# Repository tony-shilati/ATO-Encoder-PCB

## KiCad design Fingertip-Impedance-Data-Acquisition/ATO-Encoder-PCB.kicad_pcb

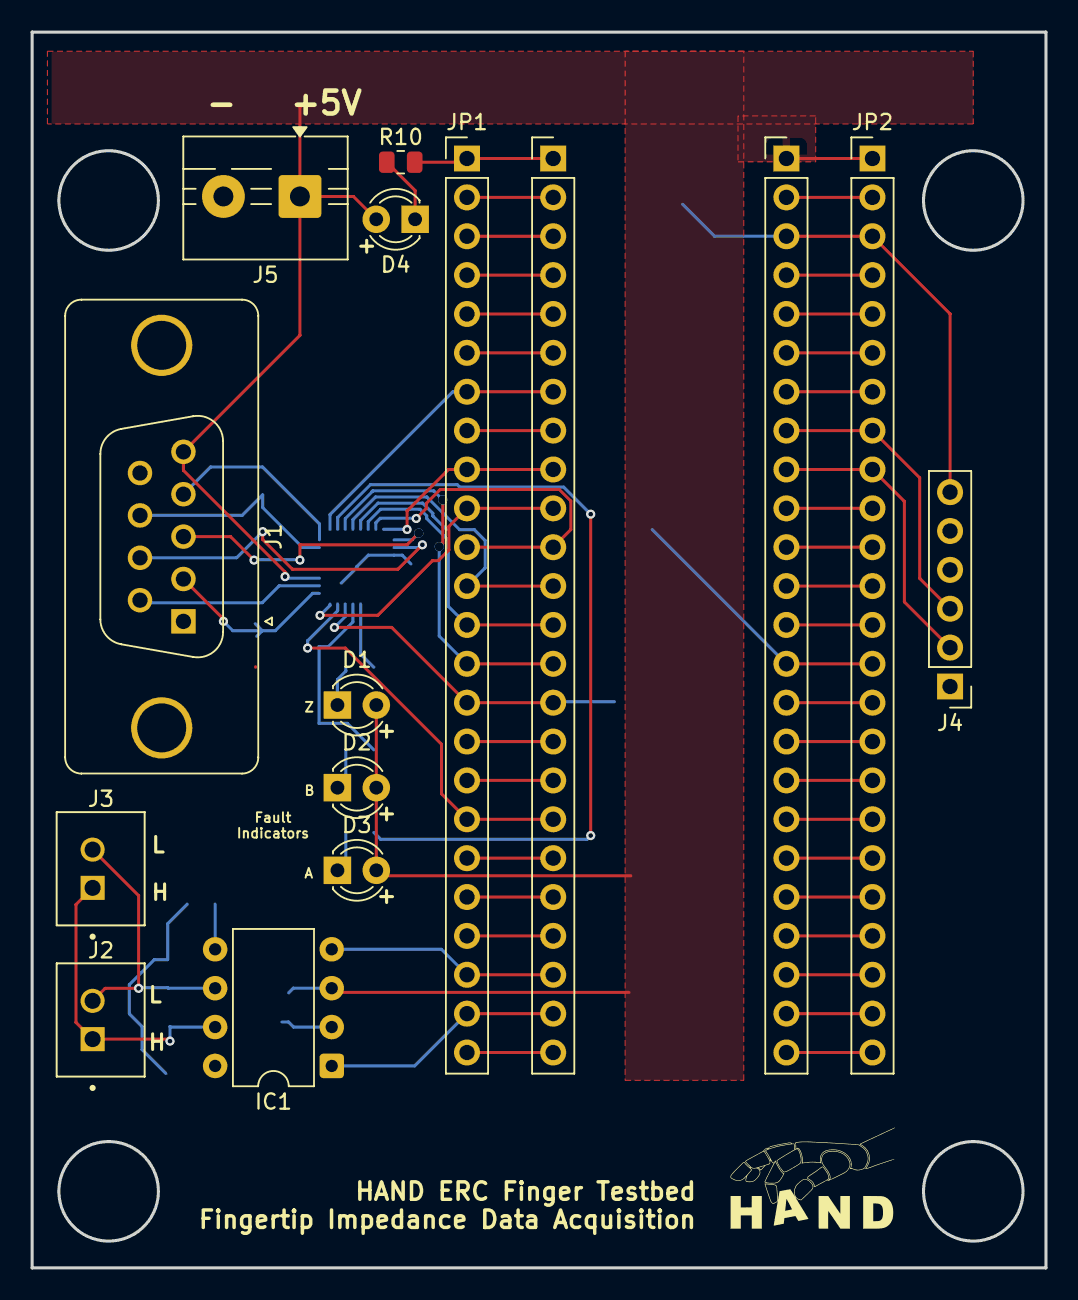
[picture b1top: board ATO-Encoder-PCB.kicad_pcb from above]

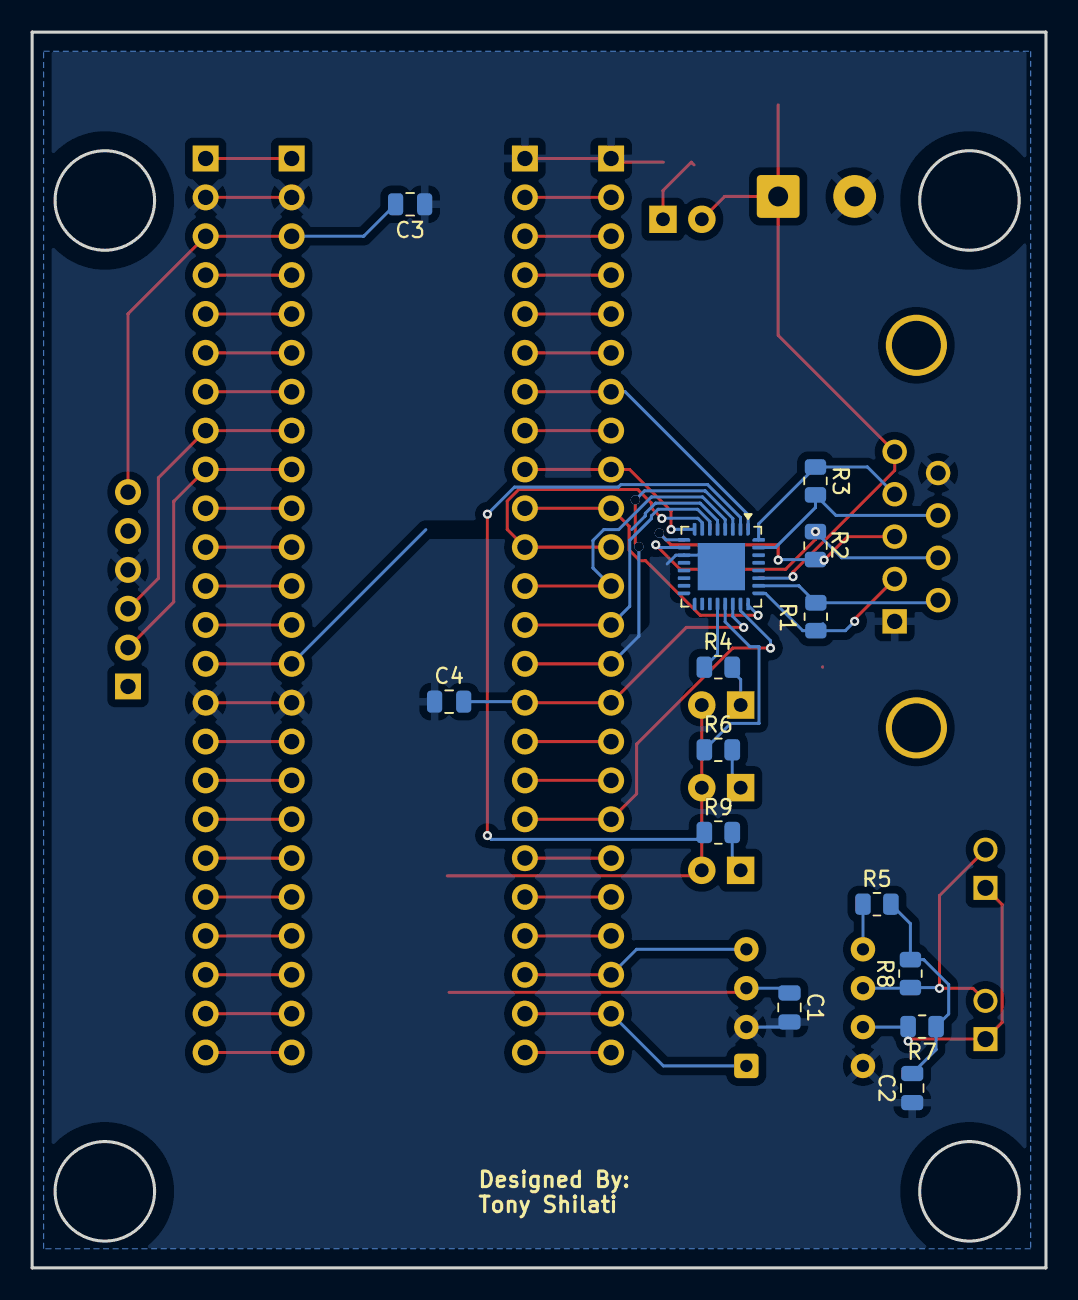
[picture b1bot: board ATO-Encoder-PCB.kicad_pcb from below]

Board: 2 copper layers, 66.2 x 80.8 mm, 28 parts (14 on the bottom side), 62 nets.

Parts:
C1: 0.1uF; C_0805_2012Metric
C2: 4700pF; C_0805_2012Metric
C3, C4: 3.3uF; C_0805_2012Metric
D1, D2, D3, D4: LED; LED_D3.0mm
IC1: MCP2561-H_P; DIP-8_W7.62mm
J1: DE9_Socket; DSUB-9_Socket_Vertical_P2.77x2.84mm_MountingHoles
J2, J3: B2B-XH-A; JST_B2B-XH-A
J4: Conn_01x06; PinHeader_1x06_P2.54mm_Vertical
J5: Screw_Terminal_01x02; TerminalBlock_MaiXu_MX126-5.0-02P_1x02_P5.00mm
JP1, JP2: PINHD-1X24; PinHeader_1x24_P2.54mm_Vertical
R1, R2, R3: 120R; R_0805_2012Metric
R4, R6, R9, R10: 150R; R_0805_2012Metric
R5: 300Ohm; R_0805_2012Metric
R7, R8: 60Ohm; R_0805_2012Metric
U1: TQFN-32-1EP_5x5mm_P0.5mm_EP3.1x3.1mm
U$1: TEENSY4-1; Teensy 4.1

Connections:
+5V: C1.1, D1.2 (A), D2.2 (A), D3.2 (A), D4.2 (A), IC1.3 (VDD), J1.5, J5.1, JP2.1, U1.27 (V_{CC}), U$1.P47 (VIN)
/3v3: C3.2, C4.2, J4.6, JP1.15, JP2.3, U1.22 (V_{L}), U$1.P14 (3V3@1), U$1.P45 (3V3@2)
/CANH3: IC1.7 (CANH), J2.1, J3.1, R7.2
/CANL3: IC1.6 (CANL), J2.2, J3.2, R8.1
/CRX2: JP1.2, U$1.P1 (P0/PWM/CRX2/CS1/RX1)
/CRX3: IC1.4 (RXD), JP1.22, U$1.P21 (P30/CRX3)
/CTX2: JP1.3, U$1.P2 (P1/PWM/CTX2/MISO1/TX1)
/CTX3: IC1.1 (TXD), JP1.23, U$1.P22 (P31/CTX3)
AO: JP1.7, U1.1 (AO), U$1.P6 (P5/PWM/IN2)
BO: JP1.9, U1.8 (BO), U$1.P8 (P7/PWM/OUT1A/RX2)
CLK: JP2.14, U1.5 (CLK), U$1.P34 (PWM/SCK/(LED)P13)
CS: JP1.12, U1.4 (~CS), U$1.P11 (P10/PWM/MQSR/CS)
Encoder Fault: JP1.11, U1.7 (~IRQ), U$1.P10 (P9/PWM/OUT1C)
GND: C1.2, C2.1, C3.1, C4.1, IC1.2 (VSS), IC1.8 (STBY), J1.1, J1.9, J4.4, J5.2, JP1.1, JP2.2, JP2.15, R10.2, U1.11 (GND), U1.33 (EP), U$1.P0 (GND@1), U$1.P33 (GND@2), U$1.P46 (GND@3)
unnamed: C2.2, R5.2, R7.1, R8.2
unnamed: D1.1 (K), R4.2
unnamed: D2.1 (K), R6.2
unnamed: D3.1 (K), R9.2
unnamed: D4.1 (K), R10.1
unnamed: IC1.5 (SPLIT), R5.1
unnamed: J1.4, R3.1, U1.32 (A)
unnamed: J1.3, R2.1, U1.9 (B)
unnamed: J1.2, R1.2, U1.25 (Z)
unnamed: R9.1, U1.2 (~AFAULT)
unnamed: J1.8, R3.2, U1.31 (~A)
unnamed: R6.1, U1.21 (~BFAULT)
unnamed: J1.7, R2.2, U1.10 (~B)
unnamed: R4.1, U1.20 (~ZFAULT)
unnamed: J1.6, R1.1, U1.26 (~Z)
unnamed: JP2.17, U$1.P31 (A16/P40)
unnamed: JP2.16, U$1.P32 (A17/P41)
unnamed: JP2.6, U$1.P42 (BLCK1/RX5/A7/P21)
unnamed: JP2.21, U$1.P27 (CS/PWM/P36)
unnamed: JP2.20, U$1.P28 (CS/PWM/P37)
unnamed: JP2.19, U$1.P29 (IN1/CS1/A14/P38)
unnamed: JP2.7, U$1.P41 (LRCLK1/TX5/A6/P20)
unnamed: JP2.24, U$1.P24 (MCLK2/PWM/P33)
unnamed: JP2.18, U$1.P30 (OUT1A/MISO1/A15/P39)
unnamed: JP1.4, U$1.P3 (P2/PWM/OUT2)
unnamed: JP1.5, U$1.P4 (P3/PWM/LRCLK2)
unnamed: JP1.6, U$1.P5 (P4/PWM/BCLK2)
unnamed: JP1.8, U$1.P7 (P6/PWM/OUT1D)
unnamed: JP1.16, U$1.P15 (P24/PWM/SCL2/TX6/A10)
unnamed: JP1.17, U$1.P16 (P25/PWM/SDA2/RX6/A11)
unnamed: JP1.19, U$1.P18 (P27/SCK1/A13)
unnamed: JP1.20, U$1.P19 (P28/PWM/RX7)
unnamed: JP1.21, U$1.P20 (P29/PWM/TX7)
unnamed: JP1.24, U$1.P23 (P32/OUT1B)
unnamed: JP2.5, U$1.P43 (PWM/CTX1/A8/P22)
unnamed: JP2.4, U$1.P44 (PWM/MCLK1/CRX1/A9/P23)
unnamed: JP2.12, U$1.P36 (PWM/S/PDIF-IN/RX3/A1/P15)
unnamed: JP2.13, U$1.P35 (PWM/S/PDIF-OUT/TX3/A0/P14)
unnamed: JP2.23, U$1.P25 (RX8/P34)
unnamed: JP2.11, U$1.P37 (SCL1/RX4/A2/P16)
unnamed: JP2.10, U$1.P38 (SDA1/TX4/A3/P17)
unnamed: JP2.22, U$1.P26 (TX8/P35)
SCL: J4.3, JP2.8, U$1.P40 (PWM/SCL/A5/P19)
SDA: J4.2, JP2.9, U$1.P39 (PWM/SDA/A4/P18)
SDI: JP1.13, U1.6 (SDI), U$1.P12 (P11/PWM/CTX1/MOSI)
SDO: JP1.14, U1.3 (SDO), U$1.P13 (P12/PWM/MQSL/MISO)
SPI: JP1.18, U1.23 (SPI), U$1.P17 (P26/MOSI1/A12)
ZO: JP1.10, U1.24 (ZO), U$1.P9 (P8/PWM/IN1/TX2)

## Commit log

2025-10-02 Created a blank KiCad project
2025-10-04 Schematic complete and PCB layout in progress. Need to select specific component and update footprints. Need to update resistances for leds. Need to add power LED. Need to reorganize to shrink PCB si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
2025-10-04 Added gitignore
2025-10-05 Shrunk the board outline
2025-10-05 PBC is ready for manufacture
2025-10-06 Order has been placed with OSH Park
2025-10-06 Reorganized repo
2025-10-07 Updated design to be compatible with quadrature decoding without CPU intervention. OSH Park order was updated
2025-10-10 Fixed SPI inteface to MAX chip
2025-10-14 Minor Updates
